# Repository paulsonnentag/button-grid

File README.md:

# button-grid

An ESP32-S3 controller board for an 8×8 button matrix with 64 individually
switched 12 V LEDs. It's designed in KiCad 9 and made to be ordered from JLCPCB.

**Site with the design viewer, test results and JLCPCB downloads:** GitHub Pages
for this repo, built by `.github/workflows/pages.yml`.

## What's on the board

| Function | Implementation |
|---|---|
| MCU | ESP32-S3-WROOM-1-N8, native USB-C for flashing and serial |
| LEDs (64, not multiplexed) | 8× 74HC595 in one chain → 8× ULN2803A low-side drivers → screw terminals |
| Buttons (your diode matrix) | 8 rows + 8 columns directly on GPIOs, 100 Ω series resistors, 22 kΩ pull-ups |
| Power | 12 V wall adapter (5.5×2.1 mm, centre +, ≥ 2 A) → SS54 reverse-polarity diode → LED supply; TPS54202 buck converter → 3.3 V |
| Size | 208 × 110 mm, 2 layers |

### Wiring

- **LED terminals J11–J18** (10-pole, 3.5 mm pitch, along the top and bottom
  edges). Pins 1–8 take the cathode (−) wire of 8 LEDs. Pins 9–10 are +12 V for
  the anode (+) wires. Each LED must keep its own series resistor. Twist or
  daisy-chain the + wires of a bank so that at most 2 wires go into one screw.
  Bank 1 (J11) is LEDs 0–7, bank 2 is LEDs 8–15, and so on.
- **ROWS J3 / COLS J4** (8-pole, left edge): connect the 8 row wires and 8
  column wires of your matrix. Which way the diodes point is set in firmware,
  so either orientation works.
- **12 V** goes into the barrel jack. USB-C alone powers only the logic (enough
  to flash firmware). The LEDs need 12 V.

### ESP32 pin map (for the firmware)

| Signal | GPIO |
|---|---|
| ROW0…ROW7 | 4, 5, 6, 7, 15, 16, 17, 18 |
| COL0…COL7 | 8, 9, 10, 11, 12, 13, 14, 21 |
| 74HC595 SER (data in) / SRCLK / RCLK (latch) / OE (active low, pulled high) | 38 / 39 / 40 / 41 |
| Chain return (last 74HC595 QH′), used to self-test the chain | 42 |
| Status LED | 2 |
| USB D− / D+ | 19 / 20 |

To set LEDs, shift out 64 bits, with the bits for bank 8 first, then pulse
RCLK. A 1 turns the LED on. Drive OE low to enable the outputs. PWM on OE
dims all LEDs.

## Repository layout

```
hardware/
  button-grid.kicad_pro/.kicad_sch/.kicad_pcb, led_bank.kicad_sch   <- open these in KiCad 9
  gen/        generators: build_schematic.py, build_pcb.py (placement), finish_pcb.py (pours)
  scripts/    build.sh, route.sh, check.sh, export.sh, check_netlist.py, jlc_bom_cpl.py
site/         build_site.py -> static GitHub Pages site
```

The design was generated from Python. It uses one "LED bank" sheet that is
reused 8 times as a KiCad hierarchical sheet, so a change to that sheet applies
to all 64 channels. The output is an ordinary KiCad project:

- **Editing by hand in KiCad:** just do it, then run `hardware/scripts/check.sh`.
  Once you've edited by hand, don't re-run the generators, because they
  overwrite the files.
- **Editing through the generators:** change `hardware/gen/*.py`, then run
  `build.sh` → `route.sh` → `check.sh`.

Every script runs KiCad from the official `kicad/kicad:9.0` Docker image when
KiCad isn't installed locally. `route.sh` also needs Java 25 and the
[Freerouting](https://freerouting.app) jar.

## How the design is checked

`hardware/scripts/check.sh` runs on every push, and the results are shown on the site:

1. **ERC.** KiCad's electrical rules check on the schematic.
2. **Connectivity assertions** (`check_netlist.py`). These check the intended
   circuit pin by pin: all 64 LED channels, the 74HC595 chain order, the
   clock/latch/enable fan-out, every matrix line, USB-C CC resistors, the buck
   converter's feedback voltage, strapping pins, and LCSC numbers on every
   assembled part. The checker was tested by feeding it deliberately broken
   netlists (swapped LED wires, a broken chain), and it catches them.
3. **DRC with schematic parity.** Manufacturing limits that are safe for
   JLCPCB, a check that every net is routed, and a check that the PCB matches
   the schematic.

Recommended before ordering:

- **Breadboard test** of one channel: an ESP32 dev board, a 74HC595, a
  ULN2803 and one of your LEDs at 12 V.
- **First power-up:** connect 12 V with no LEDs attached and measure 3.3 V.
  Then flash a test firmware that walks one LED at a time, checks the chain
  through GPIO42, and prints matrix presses over USB.

## Ordering (see the site for the files)

Upload the gerber zip, then turn on PCB Assembly with the BOM and CPL files, 2
boards assembled. The screw terminals, barrel jack, buttons and header are
through-hole parts that you solder yourself (`hand-solder-parts.csv`). On
JLCPCB's placement preview, check that the chips and the USB-C connector are
rotated correctly.

**Part numbers:** the LCSC numbers were picked from JLCPCB's catalogue but
couldn't be checked against live stock while building. Check them when you
upload the BOM. Any part flagged as out of stock can be swapped for one with
the same footprint.

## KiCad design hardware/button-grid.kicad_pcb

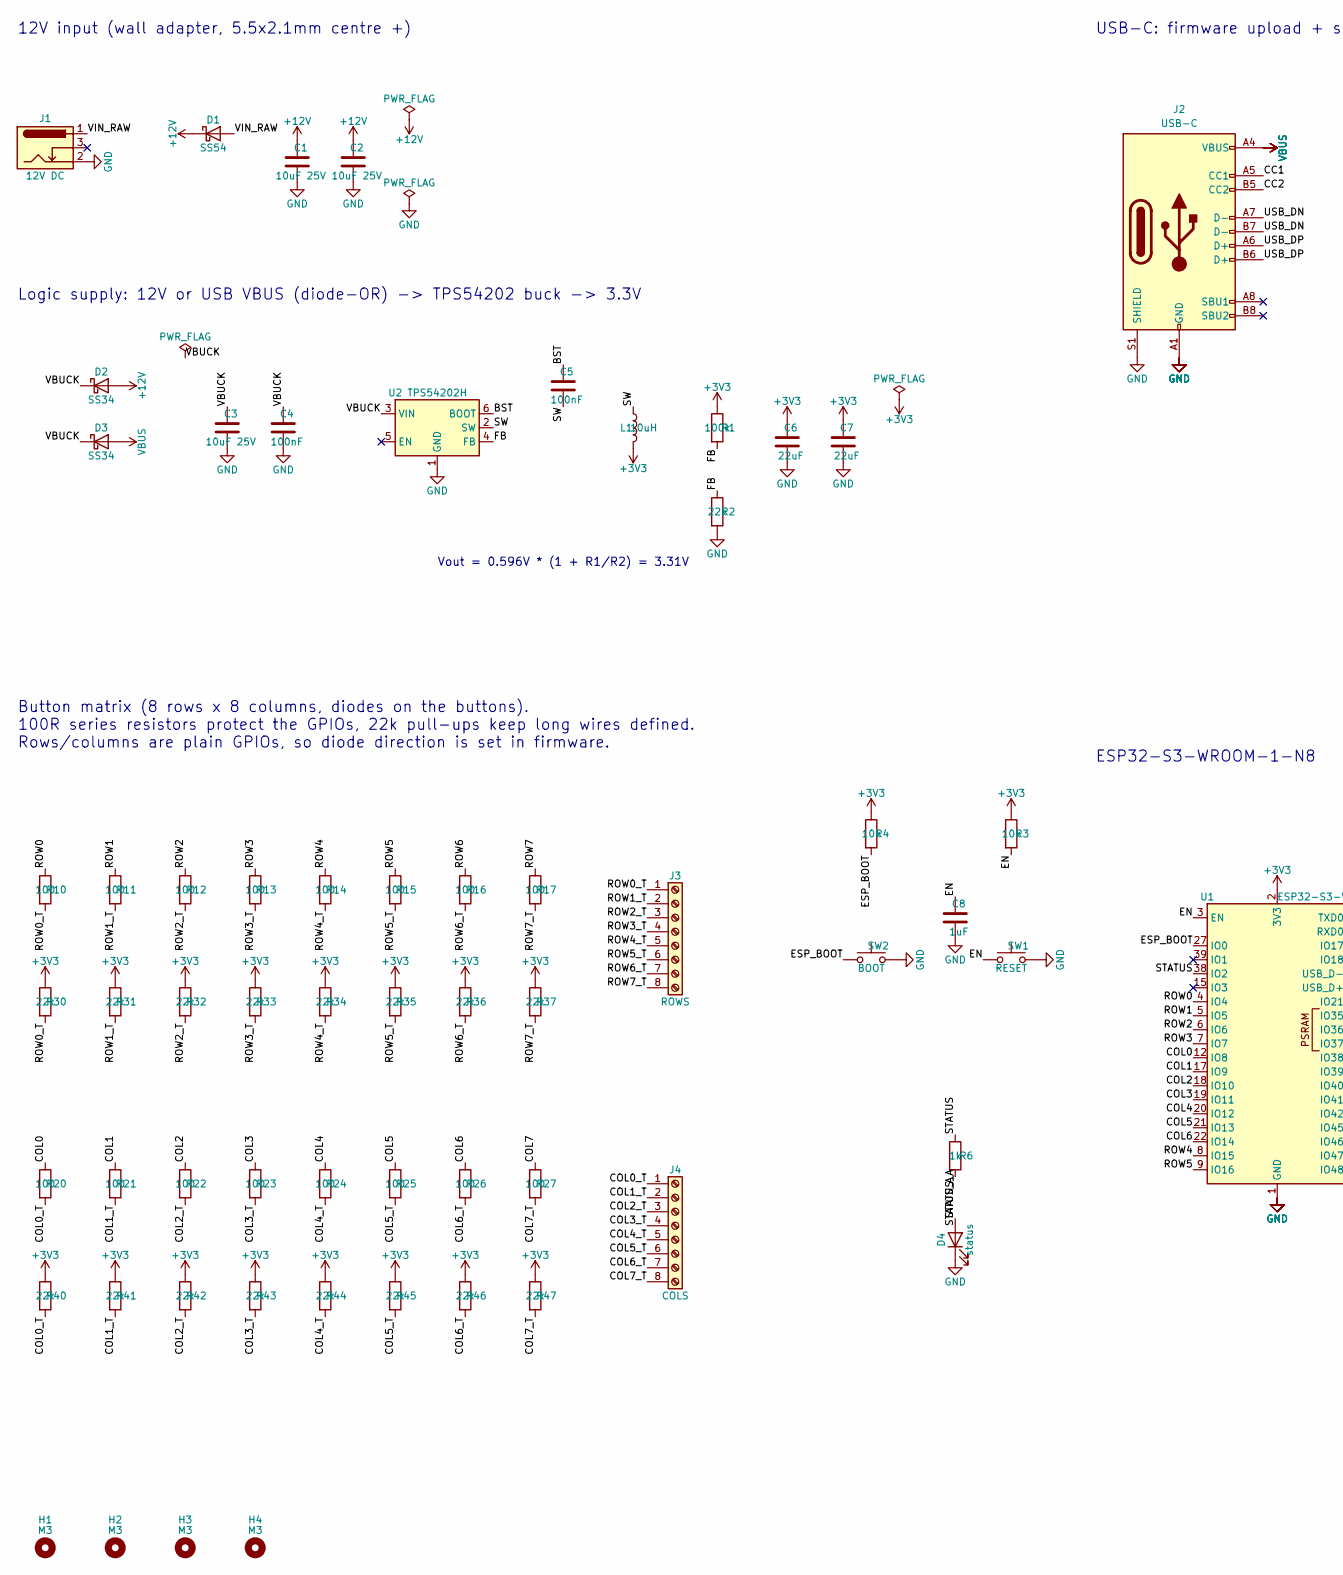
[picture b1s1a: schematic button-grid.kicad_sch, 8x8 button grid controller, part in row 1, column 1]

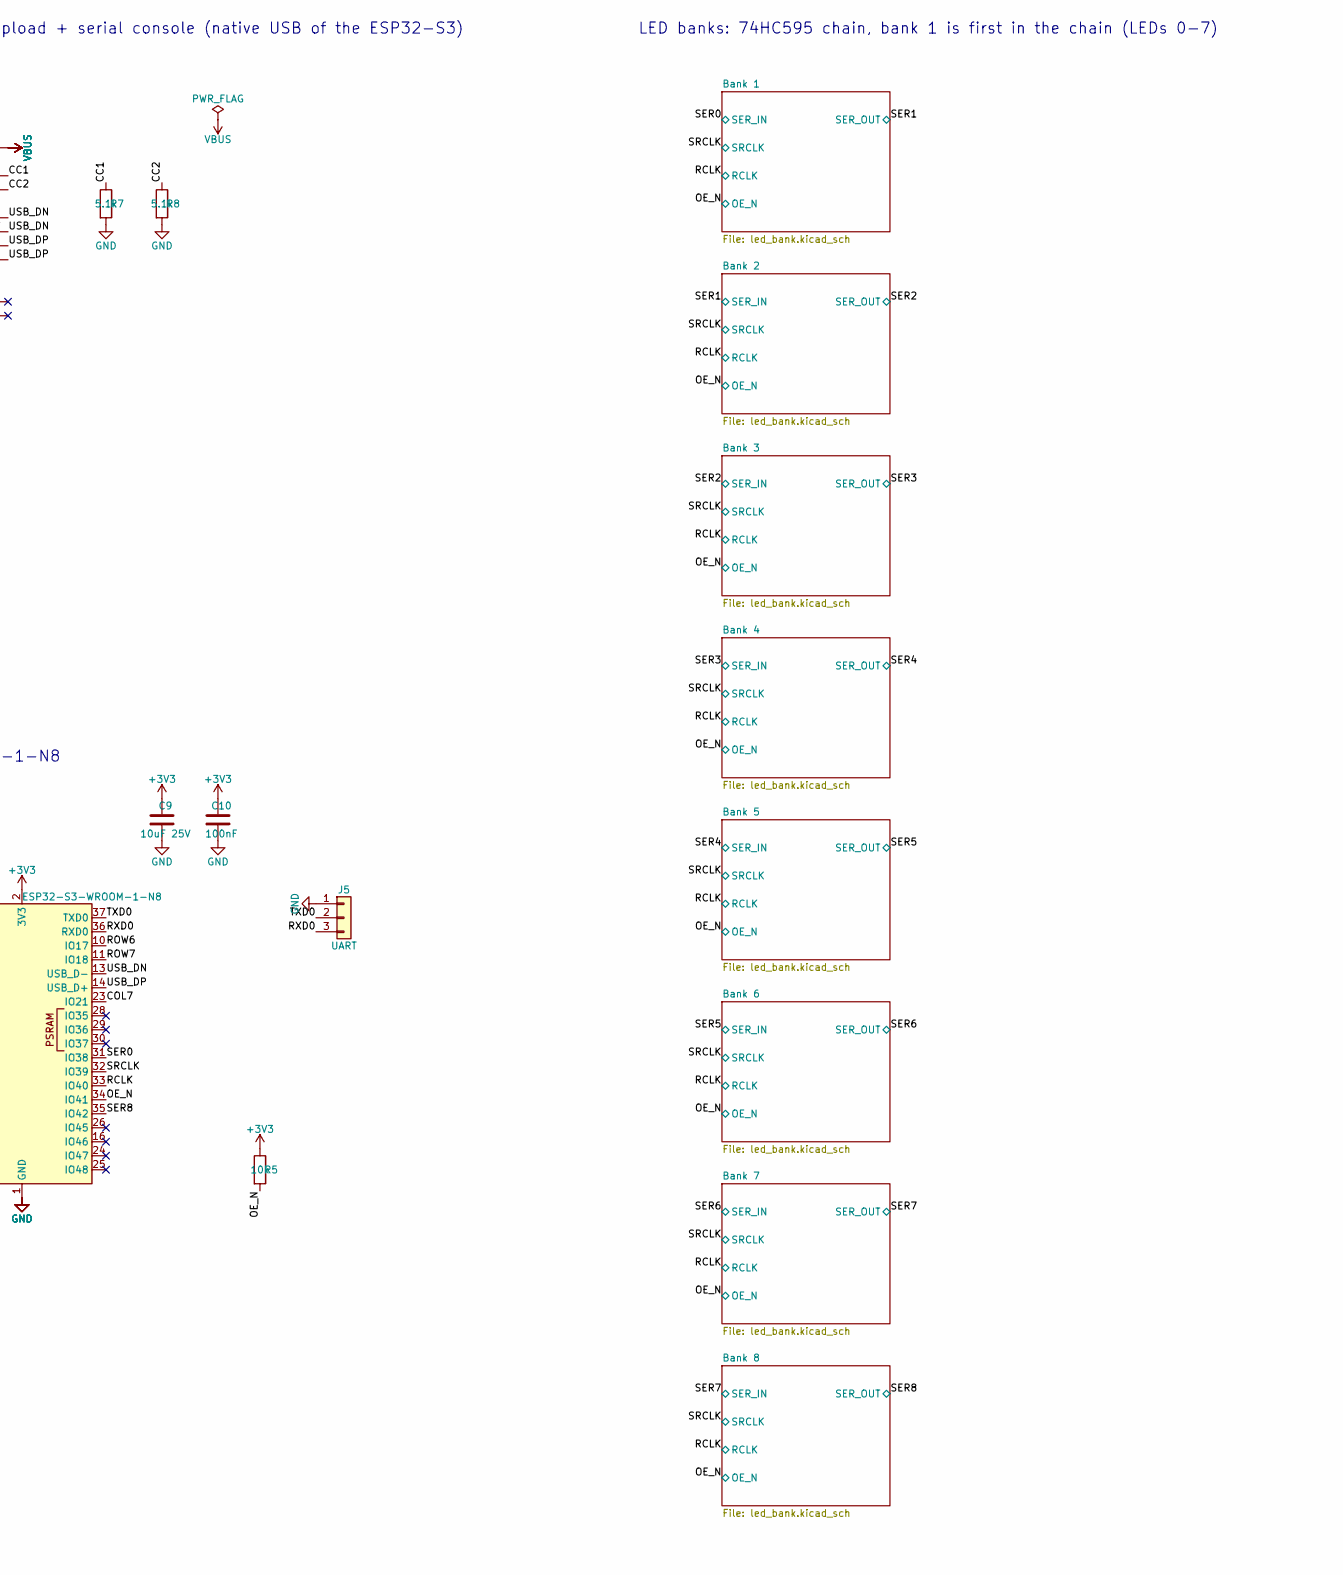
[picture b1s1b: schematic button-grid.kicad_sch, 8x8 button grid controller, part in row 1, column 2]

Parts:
C1, C2, C3, C9: 10uF 25V; C_0805_2012Metric; LCSC C15850
C4, C5, C10: 100nF; C_0603_1608Metric; LCSC C14663
C6, C7: 22uF; C_0805_2012Metric; LCSC C45783
C8: 1uF; C_0603_1608Metric; LCSC C15849
D1: SS54; D_SMA; LCSC C22452
D2, D3: SS34; D_SMA; LCSC C8678
D4: status; LED_0603_1608Metric; LCSC C2286
H1, H2, H3, H4: M3; MountingHole_3.2mm_M3
J1: 12V DC; BarrelJack_Horizontal; LCSC C381116
J2: USB-C; USB_C_Receptacle_HRO_TYPE-C-31-M-12; LCSC C165948
J3: ROWS; TerminalBlock_Phoenix_PT-1,5-8-3.5-H_1x08_P3.50mm_Horizontal
J4: COLS; TerminalBlock_Phoenix_PT-1,5-8-3.5-H_1x08_P3.50mm_Horizontal
J5: UART; PinHeader_1x03_P2.54mm_Vertical
L1: 10uH; L_Sunlord_SWPA4030S; LCSC C38117
R1: 100k; R_0603_1608Metric; LCSC C25803
R2, R30, R31, R32, R33, R34, R35, R36, R37, R40, R41, R42, R43, R44, R45, R46, R47: 22k; R_0603_1608Metric; LCSC C31850
R3, R4, R5: 10k; R_0603_1608Metric; LCSC C25804
R6: 1k; R_0603_1608Metric; LCSC C21190
R7, R8: 5.1k; R_0603_1608Metric; LCSC C23186
R10, R11, R12, R13, R14, R15, R16, R17, R20, R21, R22, R23, R24, R25, R26, R27: 100; R_0603_1608Metric; LCSC C22775
SW1: RESET; SW_PUSH_6mm
SW2: BOOT; SW_PUSH_6mm
U1: ESP32-S3-WROOM-1-N8; ESP32-S3-WROOM-1; LCSC C2913198
U2: TPS54202H; TSOT-23-6; LCSC C527684

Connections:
/BST: C5.1, U2.6 (BOOT)
/CC1: J2.A5 (CC1), R7.1
/CC2: J2.B5 (CC2), R8.1
/COL0: R20.1, U1.12 (IO8)
/COL0_T: J4.1, R20.2, R40.2
/COL1: R21.1, U1.17 (IO9)
/COL1_T: J4.2, R21.2, R41.2
/COL2: R22.1, U1.18 (IO10)
/COL2_T: J4.3, R22.2, R42.2
/COL3: R23.1, U1.19 (IO11)
/COL3_T: J4.4, R23.2, R43.2
/COL4: R24.1, U1.20 (IO12)
/COL4_T: J4.5, R24.2, R44.2
/COL5: R25.1, U1.21 (IO13)
/COL5_T: J4.6, R25.2, R45.2
/COL6: R26.1, U1.22 (IO14)
/COL6_T: J4.7, R26.2, R46.2
/COL7: R27.1, U1.23 (IO21)
/COL7_T: J4.8, R27.2, R47.2
/EN: C8.1, R3.2, SW1.1, U1.3 (EN)
/ESP_BOOT: R4.2, SW2.1, U1.27 (IO0)
/FB: R1.2, R2.1, U2.4 (FB)
/OE_N: R5.2, U1.34 (IO41); also elsewhere on the board
/RCLK: U1.33 (IO40); also elsewhere on the board
/ROW0: R10.1, U1.4 (IO4)
/ROW0_T: J3.1, R10.2, R30.2
/ROW1: R11.1, U1.5 (IO5)
/ROW1_T: J3.2, R11.2, R31.2
/ROW2: R12.1, U1.6 (IO6)
/ROW2_T: J3.3, R12.2, R32.2
/ROW3: R13.1, U1.7 (IO7)
/ROW3_T: J3.4, R13.2, R33.2
/ROW4: R14.1, U1.8 (IO15)
/ROW4_T: J3.5, R14.2, R34.2
/ROW5: R15.1, U1.9 (IO16)
/ROW5_T: J3.6, R15.2, R35.2
/ROW6: R16.1, U1.10 (IO17)
/ROW6_T: J3.7, R16.2, R36.2
/ROW7: R17.1, U1.11 (IO18)
/ROW7_T: J3.8, R17.2, R37.2
/RXD0: J5.3, U1.36 (RXD0)
/SER0: U1.31 (IO38); also elsewhere on the board
/SER8: U1.35 (IO42); also elsewhere on the board
/SRCLK: U1.32 (IO39); also elsewhere on the board
/STATUS: R6.1, U1.38 (IO2)
/STATUS_A: D4.2 (A), R6.2
/SW: C5.2, L1.1, U2.2 (SW)
/TXD0: J5.2, U1.37 (TXD0)
/USB_DN: J2.A7 (D-), J2.B7 (D-), U1.13 (USB_D-)
/USB_DP: J2.A6 (D+), J2.B6 (D+), U1.14 (USB_D+)
/VIN_RAW: D1.2 (A), J1.1

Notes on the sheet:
12V input (wall adapter, 5.5x2.1mm centre +)
Logic supply: 12V or USB VBUS (diode-OR) -> TPS54202 buck -> 3.3V
Vout = 0.596V * (1 + R1/R2) = 3.31V
USB-C: firmware upload + serial console (native USB of the ESP32-S3)
ESP32-S3-WROOM-1-N8
Button matrix (8 rows x 8 columns, diodes on the buttons). 100R series resistors protect the GPIOs, 22k pull-ups keep long wires defined. Rows/columns are plain GPIOs, so diode direction is set in firmware.
LED banks: 74HC595 chain, bank 1 is first in the chain (LEDs 0-7)

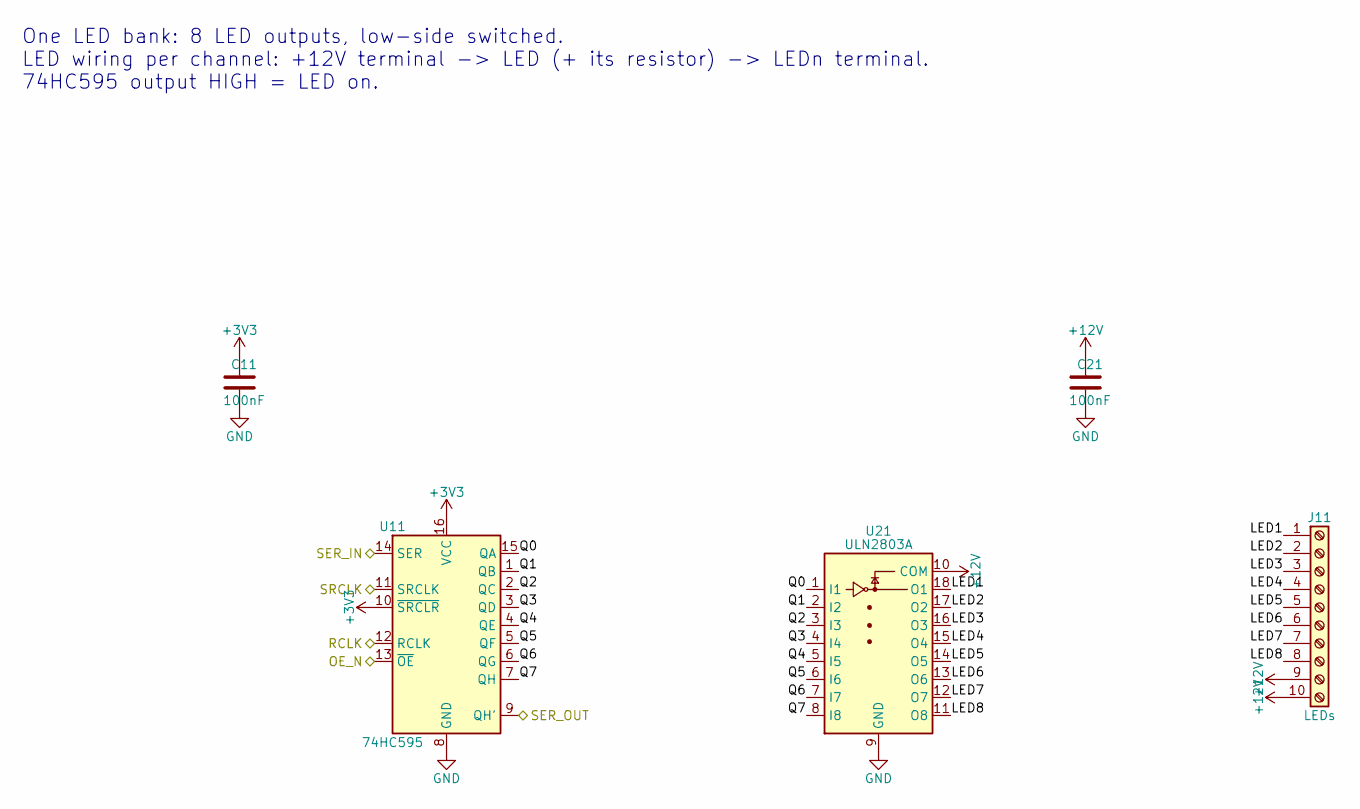
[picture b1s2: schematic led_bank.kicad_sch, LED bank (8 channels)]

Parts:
C11, C21: 100nF; C_0603_1608Metric; LCSC C14663
J11: LEDs; TerminalBlock_Phoenix_PT-1,5-10-3.5-H_1x10_P3.50mm_Horizont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
U11: 74HC595; SOIC-16_3.9x9.9mm_P1.27mm; LCSC C5947
U21: ULN2803A; SOIC-18W_7.5x11.6mm_P1.27mm; LCSC C9683

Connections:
/Bank 1/LED1: J11.1, U21.18 (O1)
/Bank 1/LED2: J11.2, U21.17 (O2)
/Bank 1/LED3: J11.3, U21.16 (O3)
/Bank 1/LED4: J11.4, U21.15 (O4)
/Bank 1/LED5: J11.5, U21.14 (O5)
/Bank 1/LED6: J11.6, U21.13 (O6)
/Bank 1/LED7: J11.7, U21.12 (O7)
/Bank 1/LED8: J11.8, U21.11 (O8)
/Bank 1/Q0: U11.15 (QA), U21.1 (I1)
/Bank 1/Q1: U11.1 (QB), U21.2 (I2)
/Bank 1/Q2: U11.2 (QC), U21.3 (I3)
/Bank 1/Q3: U11.3 (QD), U21.4 (I4)
/Bank 1/Q4: U11.4 (QE), U21.5 (I5)
/Bank 1/Q5: U11.5 (QF), U21.6 (I6)
/Bank 1/Q6: U11.6 (QG), U21.7 (I7)
/Bank 1/Q7: U11.7 (QH), U21.8 (I8)
/OE_N: U11.13 (~OE); also elsewhere on the board
/RCLK: U11.12 (RCLK); also elsewhere on the board
/SER0: U11.14 (SER); also elsewhere on the board
/SER1: U11.9 (QH'); also elsewhere on the board
/SRCLK: U11.11 (SRCLK); also elsewhere on the board

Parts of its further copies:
C12, C13, C14, C15, C16, C17, C18, C22, C23, C24, C25, C26, C27, C28: 100nF; C_0603_1608Metric; LCSC C14663
J12, J13, J14, J15, J16, J17, J18: LEDs; TerminalBlock_Phoenix_PT-1,5-10-3.5-H_1x10_P3.50mm_Horizont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
U12, U13, U14, U15, U16, U17, U18: 74HC595; SOIC-16_3.9x9.9mm_P1.27mm; LCSC C5947
U22, U23, U24, U25, U26, U27, U28: ULN2803A; SOIC-18W_7.5x11.6mm_P1.27mm; LCSC C9683

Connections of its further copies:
/Bank 2/LED1: J12.1, U22.18 (O1)
/Bank 2/LED2: J12.2, U22.17 (O2)
/Bank 2/LED3: J12.3, U22.16 (O3)
/Bank 2/LED4: J12.4, U22.15 (O4)
/Bank 2/LED5: J12.5, U22.14 (O5)
/Bank 2/LED6: J12.6, U22.13 (O6)
/Bank 2/LED7: J12.7, U22.12 (O7)
/Bank 2/LED8: J12.8, U22.11 (O8)
/Bank 2/Q0: U12.15 (QA), U22.1 (I1)
/Bank 2/Q1: U12.1 (QB), U22.2 (I2)
/Bank 2/Q2: U12.2 (QC), U22.3 (I3)
/Bank 2/Q3: U12.3 (QD), U22.4 (I4)
/Bank 2/Q4: U12.4 (QE), U22.5 (I5)
/Bank 2/Q5: U12.5 (QF), U22.6 (I6)
/Bank 2/Q6: U12.6 (QG), U22.7 (I7)
/Bank 2/Q7: U12.7 (QH), U22.8 (I8)
/Bank 3/LED1: J13.1, U23.18 (O1)
/Bank 3/LED2: J13.2, U23.17 (O2)
/Bank 3/LED3: J13.3, U23.16 (O3)
/Bank 3/LED4: J13.4, U23.15 (O4)
/Bank 3/LED5: J13.5, U23.14 (O5)
/Bank 3/LED6: J13.6, U23.13 (O6)
/Bank 3/LED7: J13.7, U23.12 (O7)
/Bank 3/LED8: J13.8, U23.11 (O8)
/Bank 3/Q0: U13.15 (QA), U23.1 (I1)
/Bank 3/Q1: U13.1 (QB), U23.2 (I2)
/Bank 3/Q2: U13.2 (QC), U23.3 (I3)
/Bank 3/Q3: U13.3 (QD), U23.4 (I4)
/Bank 3/Q4: U13.4 (QE), U23.5 (I5)
/Bank 3/Q5: U13.5 (QF), U23.6 (I6)
/Bank 3/Q6: U13.6 (QG), U23.7 (I7)
/Bank 3/Q7: U13.7 (QH), U23.8 (I8)
/Bank 4/LED1: J14.1, U24.18 (O1)
/Bank 4/LED2: J14.2, U24.17 (O2)
/Bank 4/LED3: J14.3, U24.16 (O3)
/Bank 4/LED4: J14.4, U24.15 (O4)
/Bank 4/LED5: J14.5, U24.14 (O5)
/Bank 4/LED6: J14.6, U24.13 (O6)
/Bank 4/LED7: J14.7, U24.12 (O7)
/Bank 4/LED8: J14.8, U24.11 (O8)
/Bank 4/Q0: U14.15 (QA), U24.1 (I1)
/Bank 4/Q1: U14.1 (QB), U24.2 (I2)
/Bank 4/Q2: U14.2 (QC), U24.3 (I3)
/Bank 4/Q3: U14.3 (QD), U24.4 (I4)
/Bank 4/Q4: U14.4 (QE), U24.5 (I5)
/Bank 4/Q5: U14.5 (QF), U24.6 (I6)
/Bank 4/Q6: U14.6 (QG), U24.7 (I7)
/Bank 4/Q7: U14.7 (QH), U24.8 (I8)
/Bank 5/LED1: J15.1, U25.18 (O1)
/Bank 5/LED2: J15.2, U25.17 (O2)
/Bank 5/LED3: J15.3, U25.16 (O3)
/Bank 5/LED4: J15.4, U25.15 (O4)
/Bank 5/LED5: J15.5, U25.14 (O5)
/Bank 5/LED6: J15.6, U25.13 (O6)
/Bank 5/LED7: J15.7, U25.12 (O7)
/Bank 5/LED8: J15.8, U25.11 (O8)
/Bank 5/Q0: U15.15 (QA), U25.1 (I1)
/Bank 5/Q1: U15.1 (QB), U25.2 (I2)
/Bank 5/Q2: U15.2 (QC), U25.3 (I3)
/Bank 5/Q3: U15.3 (QD), U25.4 (I4)
/Bank 5/Q4: U15.4 (QE), U25.5 (I5)
/Bank 5/Q5: U15.5 (QF), U25.6 (I6)
/Bank 5/Q6: U15.6 (QG), U25.7 (I7)
/Bank 5/Q7: U15.7 (QH), U25.8 (I8)
/Bank 6/LED1: J16.1, U26.18 (O1)
/Bank 6/LED2: J16.2, U26.17 (O2)
/Bank 6/LED3: J16.3, U26.16 (O3)
/Bank 6/LED4: J16.4, U26.15 (O4)
/Bank 6/LED5: J16.5, U26.14 (O5)
/Bank 6/LED6: J16.6, U26.13 (O6)
/Bank 6/LED7: J16.7, U26.12 (O7)
/Bank 6/LED8: J16.8, U26.11 (O8)
/Bank 6/Q0: U16.15 (QA), U26.1 (I1)
/Bank 6/Q1: U16.1 (QB), U26.2 (I2)
/Bank 6/Q2: U16.2 (QC), U26.3 (I3)
/Bank 6/Q3: U16.3 (QD), U26.4 (I4)
/Bank 6/Q4: U16.4 (QE), U26.5 (I5)
/Bank 6/Q5: U16.5 (QF), U26.6 (I6)
/Bank 6/Q6: U16.6 (QG), U26.7 (I7)
/Bank 6/Q7: U16.7 (QH), U26.8 (I8)
/Bank 7/LED1: J17.1, U27.18 (O1)
/Bank 7/LED2: J17.2, U27.17 (O2)
/Bank 7/LED3: J17.3, U27.16 (O3)
/Bank 7/LED4: J17.4, U27.15 (O4)
/Bank 7/LED5: J17.5, U27.14 (O5)
/Bank 7/LED6: J17.6, U27.13 (O6)
/Bank 7/LED7: J17.7, U27.12 (O7)
/Bank 7/LED8: J17.8, U27.11 (O8)
/Bank 7/Q0: U17.15 (QA), U27.1 (I1)
/Bank 7/Q1: U17.1 (QB), U27.2 (I2)
/Bank 7/Q2: U17.2 (QC), U27.3 (I3)
/Bank 7/Q3: U17.3 (QD), U27.4 (I4)
/Bank 7/Q4: U17.4 (QE), U27.5 (I5)
/Bank 7/Q5: U17.5 (QF), U27.6 (I6)
/Bank 7/Q6: U17.6 (QG), U27.7 (I7)
/Bank 7/Q7: U17.7 (QH), U27.8 (I8)
/Bank 8/LED1: J18.1, U28.18 (O1)
/Bank 8/LED2: J18.2, U28.17 (O2)
/Bank 8/LED3: J18.3, U28.16 (O3)
/Bank 8/LED4: J18.4, U28.15 (O4)
/Bank 8/LED5: J18.5, U28.14 (O5)
/Bank 8/LED6: J18.6, U28.13 (O6)
/Bank 8/LED7: J18.7, U28.12 (O7)
/Bank 8/LED8: J18.8, U28.11 (O8)
/Bank 8/Q0: U18.15 (QA), U28.1 (I1)
/Bank 8/Q1: U18.1 (QB), U28.2 (I2)
/Bank 8/Q2: U18.2 (QC), U28.3 (I3)
/Bank 8/Q3: U18.3 (QD), U28.4 (I4)
/Bank 8/Q4: U18.4 (QE), U28.5 (I5)
/Bank 8/Q5: U18.5 (QF), U28.6 (I6)
/Bank 8/Q6: U18.6 (QG), U28.7 (I7)
/Bank 8/Q7: U18.7 (QH), U28.8 (I8)
/OE_N: U12.13 (~OE), U13.13 (~OE), U14.13 (~OE), U15.13 (~OE), U16.13 (~OE), U17.13 (~OE), U18.13 (~OE); also elsewhere on the board
/RCLK: U12.12 (RCLK), U13.12 (RCLK), U14.12 (RCLK), U15.12 (RCLK), U16.12 (RCLK), U17.12 (RCLK), U18.12 (RCLK); also elsewhere on the board
/SER1: U12.14 (SER); also elsewhere on the board
/SER2: U12.9 (QH'), U13.14 (SER)
/SER3: U13.9 (QH'), U14.14 (SER)
/SER4: U14.9 (QH'), U15.14 (SER)
/SER5: U15.9 (QH'), U16.14 (SER)
/SER6: U16.9 (QH'), U17.14 (SER)
/SER7: U17.9 (QH'), U18.14 (SER)
/SER8: U18.9 (QH'); also elsewhere on the board
/SRCLK: U12.11 (SRCLK), U13.11 (SRCLK), U14.11 (SRCLK), U15.11 (SRCLK), U16.11 (SRCLK), U17.11 (SRCLK), U18.11 (SRCLK); also elsewhere on the board

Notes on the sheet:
One LED bank: 8 LED outputs, low-side switched. LED wiring per channel: +12V terminal -> LED (+ its resistor) -> LEDn terminal. 74HC595 output HIGH = LED on.

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
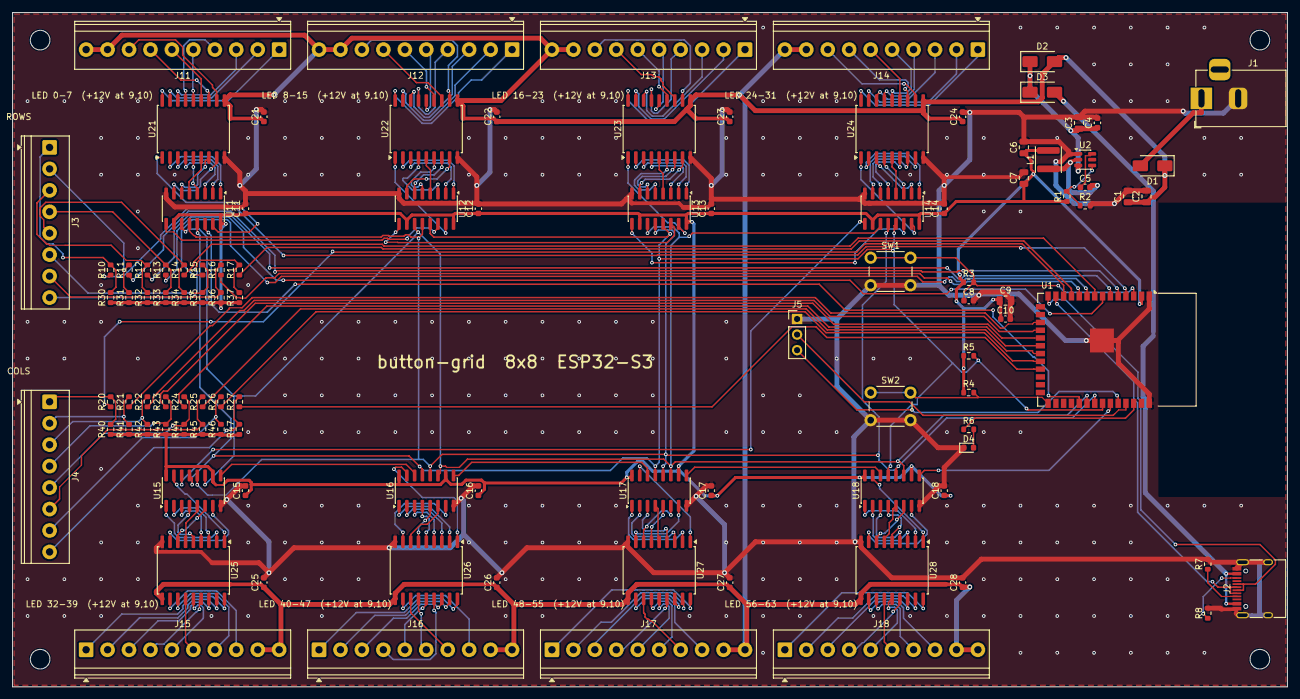
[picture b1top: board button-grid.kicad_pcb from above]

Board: 2 copper layers, 208.0 x 110.0 mm, 108 parts (0 on the bottom side), 191 nets.
